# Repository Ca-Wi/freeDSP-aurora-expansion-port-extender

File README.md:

# freeDSP aurora expansion port extender and 3V3 PS

PCB to expand the freeDSP aurora expansion port with 3V3 regulator

## Contributing

**Please take care on which branch you're currently working!**

Branches:

- *master* - this branch always holds the latest released revision
- *develop* - this is the develop branch with new features. Please base your patches on this branch.

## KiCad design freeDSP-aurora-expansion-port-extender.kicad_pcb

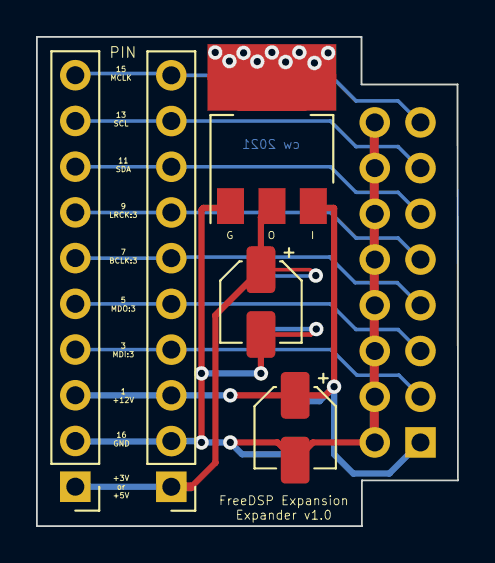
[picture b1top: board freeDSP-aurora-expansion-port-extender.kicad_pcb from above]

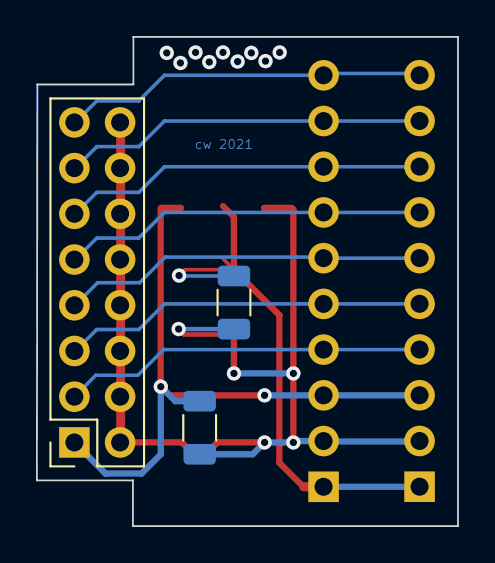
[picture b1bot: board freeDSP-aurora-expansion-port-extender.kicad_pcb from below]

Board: 2 copper layers, 23.4 x 27.2 mm, 8 parts (3 on the bottom side), 10 nets.

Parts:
C1, C2: CP_Elec_4x5.4
C11, C22: C_1206_3216Metric
J2: PinSocket_2x08_P2.54mm_Vertical
J4, J4#2: PinHeader_1x10_P2.54mm_Vertical
U1: SOT-223-3_TabPin2

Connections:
+3V3: C2.1, C22.1, J4.0, J4#2.0, U1.2
+12V: C1.1, C11.1, J2.1, J4.2, J4#2.2, U1.3
BCLK:3: J2.7, J4.5, J4#2.5
GND: C1.2, C2.2, C11.2, C22.2, J2.2, J2.4, J2.6, J2.8, J2.10, J2.12, J2.14, J2.16, J4.1, J4#2.1, U1.1
LRCK:3: J2.9, J4.6, J4#2.6
MCLK: J2.15, J4.9, J4#2.9
MDI:3: J2.3, J4.3, J4#2.3
MDO:3: J2.5, J4.4, J4#2.4
SCL: J2.13, J4.8, J4#2.8
SDA: J2.11, J4.7, J4#2.7

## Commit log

2022-03-06 v1.0
